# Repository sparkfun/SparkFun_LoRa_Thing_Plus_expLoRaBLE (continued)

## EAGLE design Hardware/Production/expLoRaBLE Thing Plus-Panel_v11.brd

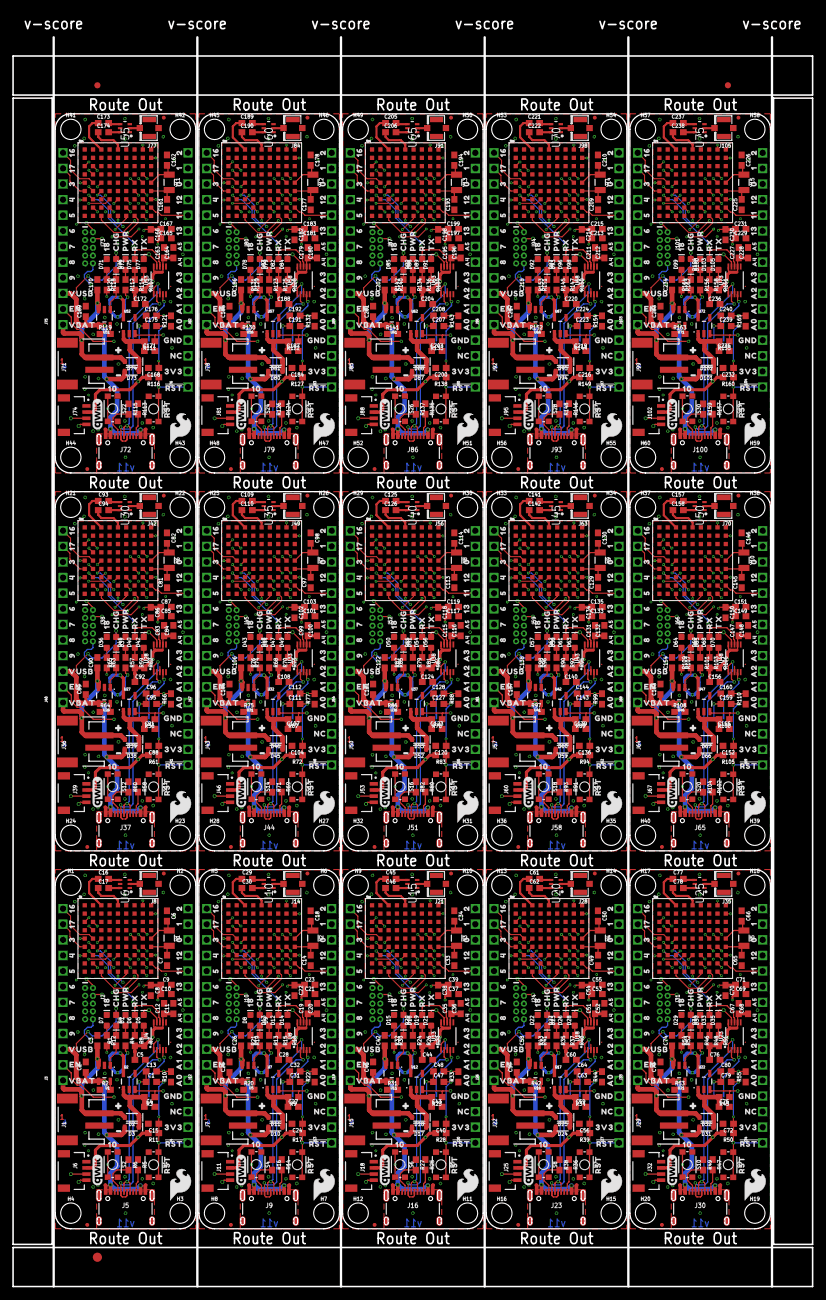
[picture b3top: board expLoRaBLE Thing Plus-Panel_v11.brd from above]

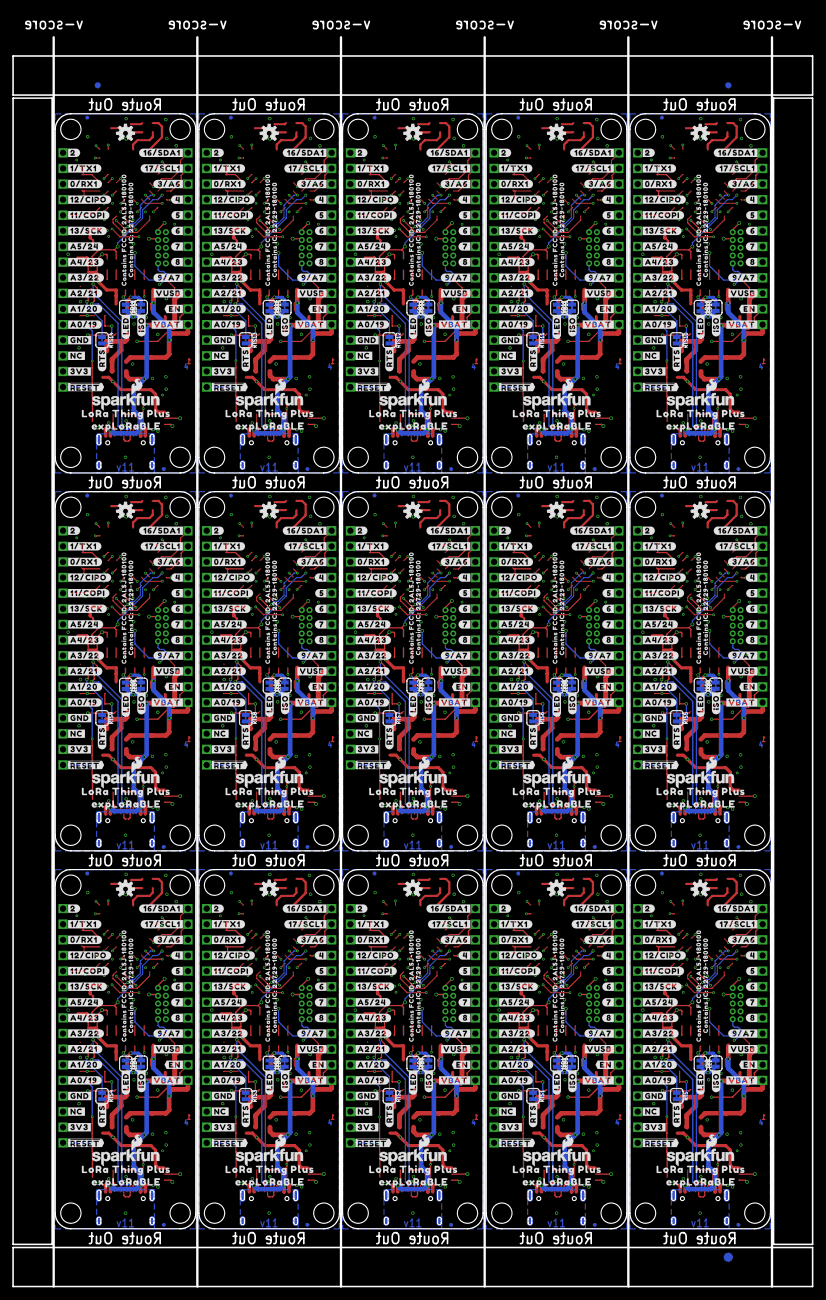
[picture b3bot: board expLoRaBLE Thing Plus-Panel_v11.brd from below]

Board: 4 copper layers, 130.0 x 203.2 mm, 2181 parts (633 on the bottom side), 900 nets.

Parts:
C1, C10, C11, C13, C20, C21, C31, C32, C36, C37, C47, C48, C52, C53, C63, C64, C68, C69, C79, C80, C84, C85, C95, C96, C100, C101, C111, C112, C116, C117, C127, C128, C132, C133, C143, C144, C148, C149, C159, C160, C164, C165, C175, C176, C180, C181, C191, C192, C196, C197, C207, C208, C212, C213, C223, C224, C228, C229, C239, C240: 0.1uF; 0603
C2, C3, C25, C26, C41, C42, C57, C58, C73, C74, C89, C90, C105, C106, C121, C122, C137, C138, C153, C154, C169, C170, C185, C186, C201, C202, C217, C218, C233, C234: 4.7uF; 0603
C4, C5, C9, C23, C27, C28, C39, C43, C44, C55, C59, C60, C71, C75, C76, C87, C91, C92, C103, C107, C108, C119, C123, C124, C135, C139, C140, C151, C155, C156, C167, C171, C172, C183, C187, C188, C199, C203, C204, C215, C219, C220, C231, C235, C236: 1.0uF; 0603
C6, C7, C14, C18, C33, C34, C49, C50, C65, C66, C81, C82, C97, C98, C113, C114, C129, C130, C145, C146, C161, C162, C177, C178, C193, C194, C209, C210, C225, C226: 15pF; 0603
C8, C22, C38, C54, C70, C86, C102, C118, C134, C150, C166, C182, C198, C214, C230: 10uF; 0603
C12, C19, C35, C51, C67, C83, C99, C115, C131, C147, C163, C179, C195, C211, C227: 10nF; 0603
C15, C24, C40, C56, C72, C88, C104, C120, C136, C152, C168, C184, C200, C216, C232: 1nF; 0603
C16, C29, C45, C61, C77, C93, C109, C125, C141, C157, C173, C189, C205, C221, C237: 47pF; 0603
C17, C30, C46, C62, C78, C94, C110, C126, C142, C158, C174, C190, C206, C222, C238: 10pF; 0603
D1, D6, D9, D12, D16, D19, D23, D26, D30, D33, D37, D40, D44, D47, D51, D54, D58, D61, D65, D68, D72, D75, D79, D82, D86, D89, D93, D96, D100, D103: Yellow; LED-0603
D2, D3, D10, D11, D17, D18, D24, D25, D31, D32, D38, D39, D45, D46, D52, D53, D59, D60, D66, D67, D73, D74, D80, D81, D87, D88, D94, D95, D101, D102: 3A/10V/280mV; SOD-323
D4, D13, D20, D27, D34, D41, D48, D55, D62, D69, D76, D83, D90, D97, D104: RED; LED-0603
D5, D14, D21, D28, D35, D42, D49, D56, D63, D70, D77, D84, D91, D98, D105: GREEN; LED-0603
D7, D8, D15, D22, D29, D36, D43, D50, D57, D64, D71, D78, D85, D92, D99: BLUE; LED-0603
E$1, E$2, E$3, E$4: FIDUCIAL-1X2
E$5, E$6: FIDUCIAL-1.5X3
FD1, FD2, FD3, FD4, FD5, FD6, FD7, FD8, FD9, FD10, FD11, FD12, FD13, FD14, FD15, FD16, FD17, FD18, FD19, FD20, FD21, FD22, FD23, FD24, FD25, FD26, FD27, FD28, FD29, FD30, FD31, FD32, FD33, FD34, FD35, FD36, FD37, FD38, FD39, FD40, FD41, FD42, FD43, FD44, FD45, FD46, FD47, FD48, FD49, FD50, FD51, FD52, FD53, FD54, FD55, FD56, FD57, FD58, FD59, FD60: FIDUCIALUFIDUCIAL; FIDUCIAL-MICRO
FRAME1, FRAME3, FRAME5, FRAME7, FRAME9, FRAME11, FRAME13, FRAME15, FRAME17, FRAME19, FRAME21, FRAME23, FRAME25, FRAME27, FRAME29: FRAME-LETTER; CREATIVE_COMMONS
FRAME2, FRAME4, FRAME6, FRAME8, FRAME10, FRAME12, FRAME14, FRAME16, FRAME18, FRAME20, FRAME22, FRAME24, FRAME26, FRAME28, FRAME30: FRAME-LETTERNO_PACKAGE; DUMMY
H1, H2, H3, H4, H5, H6, H7, H8, H9, H10, H11, H12, H13, H14, H15, H16, H17, H18, H19, H20, H21, H22, H23, H24, H25, H26, H27, H28, H29, H30, H31, H32, H33, H34, H35, H36, H37, H38, H39, H40, H41, H42, H43, H44, H45, H46, H47, H48, H49, H50, H51, H52, H53, H54, H55, H56, H57, H58, H59, H60: STAND-OFF
ISO, ISO1, ISO2, ISO3, ISO4, ISO5, ISO6, ISO7, ISO8, ISO9, ISO10, ISO11, ISO12, ISO13, ISO14: JUMPER-SMT_2_NC_TRACE_SILK; SMT-JUMPER_2_NC_TRACE_SILK
J1, J7, J15, J22, J29, J36, J43, J50, J57, J64, J71, J78, J85, J92, J99: JST-2-SMD
J2, J10, J17, J24, J31, J38, J45, J52, J59, J66, J73, J80, J87, J94, J101: CORTEX_DEBUG; 2X5-PTH-1.27MM-NO_SILK
J3, J12, J19, J26, J33, J40, J47, J54, J61, J68, J75, J82, J89, J96, J103: 1X12_SM_SQ_NOSILK
J4, J13, J20, J27, J34, J41, J48, J55, J62, J69, J76, J83, J90, J97, J104: 1X16_SM_SQ_NOSILK
J5, J9, J16, J23, J30, J37, J44, J51, J58, J65, J72, J79, J86, J93, J100: USB Female Type C Connector; USB-C-16P-4LAYER-ISOLATED
J6, J11, J18, J25, J32, J39, J46, J53, J60, J67, J74, J81, J88, J95, J102: QWIIC_RA; JST04_1MM_RA
J8, J14, J21, J28, J35, J42, J49, J56, J63, J70, J77, J84, J91, J98, J105: U.FL
LED, LED1, LED2, LED3, LED4, LED5, LED6, LED7, LED8, LED9, LED10, LED11, LED12, LED13, LED14: JUMPER-SMT_2_NC_TRACE_SILK; SMT-JUMPER_2_NC_TRACE_SILK
LOGO1, LOGO6, LOGO9, LOGO12, LOGO15, LOGO18, LOGO21, LOGO24, LOGO27, LOGO30, LOGO33, LOGO36, LOGO39, LOGO42, LOGO45: OSHW-LOGOS; OSHW-LOGO-S
LOGO2, LOGO4, LOGO7, LOGO10, LOGO13, LOGO16, LOGO19, LOGO22, LOGO25, LOGO28, LOGO31, LOGO34, LOGO37, LOGO40, LOGO43: QWIIC_LOGO_5MM; QWIIC_5MM
LOGO3, LOGO5, LOGO8, LOGO11, LOGO14, LOGO17, LOGO20, LOGO23, LOGO26, LOGO29, LOGO32, LOGO35, LOGO38, LOGO41, LOGO44: SFE_LOGO_NAME_FLAME.1_INCH; SFE_LOGO_NAME_FLAME_.1
R1, R4, R7, R8, R12, R13, R15, R18, R19, R21, R24, R26, R29, R30, R32, R35, R37, R40, R41, R43, R46, R48, R51, R52, R54, R57, R59, R62, R63, R65, R68, R70, R73, R74, R76, R79, R81, R84, R85, R87, R90, R92, R95, R96, R98, R101, R103, R106, R107, R109, R112, R114, R117, R118, R120, R123, R125, R128, R129, R131, R134, R136, R139, R140, R142, R145, R147, R150, R151, R153, R156, R158, R161, R162, R164: 1k; 0603
R2, R20, R31, R42, R53, R64, R75, R86, R97, R108, R119, R130, R141, R152, R163: 2.0k; 0603
R3, R9, R23, R34, R45, R56, R67, R78, R89, R100, R111, R122, R133, R144, R155: 10k; 0603
R5, R6, R14, R16, R25, R27, R36, R38, R47, R49, R58, R60, R69, R71, R80, R82, R91, R93, R102, R104, R113, R115, R124, R126, R135, R137, R146, R148, R157, R159: 5.1k; 0603
R10, R22, R33, R44, R55, R66, R77, R88, R99, R110, R121, R132, R143, R154, R165: 220k; 0603
R11, R17, R28, R39, R50, R61, R72, R83, R94, R105, R116, R127, R138, R149, R160: 100k; 0603
RTS, RTS1, RTS2, RTS3, RTS4, RTS5, RTS6, RTS7, RTS8, RTS9, RTS10, RTS11, RTS12, RTS13, RTS14: JUMPER-SMT_2_NC_TRACE_SILK; SMT-JUMPER_2_NC_TRACE_SILK
S1, S3, S5, S7, S9, S11, S13, S15, S17, S19, S21, S23, S25, S27, S29: RESET; TACTILE_SWITCH_SMD_4.6X2.8MM
S2, S4, S6, S8, S10, S12, S14, S16, S18, S20, S22, S24, S26, S28, S30: USER; TACTILE_SWITCH_SMD_4.6X2.8MM
TP1, TP2, TP3, TP4, TP5, TP6, TP7, TP8, TP9, TP10, TP11, TP12, TP13, TP14, TP15, TP16, TP17, TP18, TP19, TP20, TP21, TP22, TP23, TP24, TP25, TP26, TP27, TP28, TP29, TP30, TP31, TP32, TP33, TP34, TP35, TP36, TP37, TP38, TP39, TP40, TP41, TP42, TP43, TP44, TP45, TP46, TP47, TP48, TP49, TP50, TP51, TP52, TP53, TP54, TP55, TP56, TP57, TP58, TP59, TP60, TP61, TP62, TP63, TP64, TP65, TP66, TP67, TP68, TP69, TP70, TP71, TP72, TP73, TP74, TP75, TP76, TP77, TP78, TP79, TP80, TP81, TP82, TP83, TP84, TP85, TP86, TP87, TP88, TP89, TP90: TEST-POINTTP_15TH_THRU; TP_15TH
U1, U5, U11, U16, U21, U26, U31, U36, U41, U46, U51, U56, U61, U66, U71: MCP73831; SOT23-5
U2, U7, U12, U17, U22, U27, U32, U37, U42, U47, U52, U57, U62, U67, U72: 3.3V; SOT23-5
U3, U9, U14, U19, U24, U29, U34, U39, U44, U49, U54, U59, U64, U69, U74: NM180100; LGA81
U4, U8, U13, U18, U23, U28, U33, U38, U43, U48, U53, U58, U63, U68, U73: CH340E_MSOP10; MSOP10
U6, U10, U15, U20, U25, U30, U35, U40, U45, U50, U55, U60, U65, U70, U75: DPX202700DT-4162A1; RF_4060A1_TDK
U$1, U$115, U$189, U$263, U$337, U$411, U$485, U$559, U$633, U$707, U$781, U$855, U$929, U$1003, U$1077: #16#SDA1#0
U$2, U$113, U$187, U$261, U$335, U$409, U$483, U$557, U$631, U$705, U$779, U$853, U$927, U$1001, U$1075: LORA_THING_PLUS0
U$3, U$114, U$188, U$262, U$336, U$410, U$484, U$558, U$632, U$706, U$780, U$854, U$928, U$1002, U$1076: EXPLORABLE0
U$4, U$116, U$190, U$264, U$338, U$412, U$486, U$560, U$634, U$708, U$782, U$856, U$930, U$1004, U$1078: #17#SCL1#0
U$5, U$117, U$191, U$265, U$339, U$413, U$487, U$561, U$635, U$709, U$783, U$857, U$931, U$1005, U$1079: #3#A6#0
U$6, U$118, U$192, U$266, U$340, U$414, U$488, U$562, U$636, U$710, U$784, U$858, U$932, U$1006, U$1080: #4#0
U$7, U$119, U$193, U$267, U$341, U$415, U$489, U$563, U$637, U$711, U$785, U$859, U$933, U$1007, U$1081: #5#0
U$8, U$120, U$194, U$268, U$342, U$416, U$490, U$564, U$638, U$712, U$786, U$860, U$934, U$1008, U$1082: #6#0
U$9, U$121, U$195, U$269, U$343, U$417, U$491, U$565, U$639, U$713, U$787, U$861, U$935, U$1009, U$1083: #7#0
U$10, U$122, U$196, U$270, U$344, U$418, U$492, U$566, U$640, U$714, U$788, U$862, U$936, U$1010, U$1084: #8#0
U$11, U$123, U$197, U$271, U$345, U$419, U$493, U$567, U$641, U$715, U$789, U$863, U$937, U$1011, U$1085: #9#A7#0
U$12, U$124, U$198, U$272, U$346, U$420, U$494, U$568, U$642, U$716, U$790, U$864, U$938, U$1012, U$1086: #VUSB#0
U$13, U$125, U$199, U$273, U$347, U$421, U$495, U$569, U$643, U$717, U$791, U$865, U$939, U$1013, U$1087: VUSB0
U$14, U$126, U$200, U$274, U$348, U$422, U$496, U$570, U$644, U$718, U$792, U$866, U$940, U$1014, U$1088: #EN#0
U$15, U$127, U$201, U$275, U$349, U$423, U$497, U$571, U$645, U$719, U$793, U$867, U$941, U$1015, U$1089: #VBAT#0
U$16, U$128, U$202, U$276, U$350, U$424, U$498, U$572, U$646, U$720, U$794, U$868, U$942, U$1016, U$1090: #2#0
U$17, U$129, U$203, U$277, U$351, U$425, U$499, U$573, U$647, U$721, U$795, U$869, U$943, U$1017, U$1091: #1#TX1#0
U$18, U$130, U$204, U$278, U$352, U$426, U$500, U$574, U$648, U$722, U$796, U$870, U$944, U$1018, U$1092: #0#RX1#0
U$19, U$131, U$205, U$279, U$353, U$427, U$501, U$575, U$649, U$723, U$797, U$871, U$945, U$1019, U$1093: #12#CIPO#0
U$20, U$132, U$206, U$280, U$354, U$428, U$502, U$576, U$650, U$724, U$798, U$872, U$946, U$1020, U$1094: #11#COPI#0
U$21, U$133, U$207, U$281, U$355, U$429, U$503, U$577, U$651, U$725, U$799, U$873, U$947, U$1021, U$1095: #13#SCK#0
U$22, U$146, U$220, U$294, U$368, U$442, U$516, U$590, U$664, U$738, U$812, U$886, U$960, U$1034, U$1108: CONTAINS_FCC_ID#_2AL5J#1801000
U$23, U$147, U$221, U$295, U$369, U$443, U$517, U$591, U$665, U$739, U$813, U$887, U$961, U$1035, U$1109: CONTAINS_IC#_22729#1801000
U$24, U$148, U$222, U$296, U$370, U$444, U$518, U$592, U$666, U$740, U$814, U$888, U$962, U$1036, U$1110: #RTS#0
U$25, U$65, U$149, U$223, U$297, U$371, U$445, U$519, U$593, U$667, U$741, U$815, U$889, U$963, U$1037: SFE_LOGO_FLAME_.2
U$26, U$64, U$150, U$224, U$298, U$372, U$446, U$520, U$594, U$668, U$742, U$816, U$890, U$964, U$1038: FOUR_LAYER_WARNING
U$27, U$66, U$151, U$225, U$299, U$373, U$447, U$521, U$595, U$669, U$743, U$817, U$891, U$965, U$1039: 160
U$28, U$134, U$208, U$282, U$356, U$430, U$504, U$578, U$652, U$726, U$800, U$874, U$948, U$1022, U$1096: #GND#0
U$29, U$135, U$209, U$283, U$357, U$431, U$505, U$579, U$653, U$727, U$801, U$875, U$949, U$1023, U$1097: #NC#0
U$30, U$136, U$210, U$284, U$358, U$432, U$506, U$580, U$654, U$728, U$802, U$876, U$950, U$1024, U$1098: #3V3#0
U$31, U$137, U$211, U$285, U$359, U$433, U$507, U$581, U$655, U$729, U$803, U$877, U$951, U$1025, U$1099: ##RESET##0
U$32, U$138, U$212, U$286, U$360, U$434, U$508, U$582, U$656, U$730, U$804, U$878, U$952, U$1026, U$1100: #LED#0
U$33, U$140, U$214, U$288, U$362, U$436, U$510, U$584, U$658, U$732, U$806, U$880, U$954, U$1028, U$1102: #A0#19#0
U$34, U$139, U$213, U$287, U$361, U$435, U$509, U$583, U$657, U$731, U$805, U$879, U$953, U$1027, U$1101: #ISO#0
U$35, U$141, U$215, U$289, U$363, U$437, U$511, U$585, U$659, U$733, U$807, U$881, U$955, U$1029, U$1103: #A1#20#0
U$36, U$142, U$216, U$290, U$364, U$438, U$512, U$586, U$660, U$734, U$808, U$882, U$956, U$1030, U$1104: #A2#21#0
U$37, U$143, U$217, U$291, U$365, U$439, U$513, U$587, U$661, U$735, U$809, U$883, U$957, U$1031, U$1105: #A3#22#0
U$38, U$144, U$218, U$292, U$366, U$440, U$514, U$588, U$662, U$736, U$810, U$884, U$958, U$1032, U$1106: #A4#23#0
U$39, U$145, U$219, U$293, U$367, U$441, U$515, U$589, U$663, U$737, U$811, U$885, U$959, U$1033, U$1107: #A5#24#0
U$40, U$69, U$152, U$226, U$300, U$374, U$448, U$522, U$596, U$670, U$744, U$818, U$892, U$966, U$1040: 170
U$41, U$70, U$153, U$227, U$301, U$375, U$449, U$523, U$597, U$671, U$745, U$819, U$893, U$967, U$1041: 30
U$42, U$71, U$154, U$228, U$302, U$376, U$450, U$524, U$598, U$672, U$746, U$820, U$894, U$968, U$1042: 40
U$43, U$72, U$155, U$229, U$303, U$377, U$451, U$525, U$599, U$673, U$747, U$821, U$895, U$969, U$1043: 50
U$44, U$73, U$156, U$230, U$304, U$378, U$452, U$526, U$600, U$674, U$748, U$822, U$896, U$970, U$1044: 60
U$45, U$74, U$157, U$231, U$305, U$379, U$453, U$527, U$601, U$675, U$749, U$823, U$897, U$971, U$1045: 70
U$46, U$75, U$158, U$232, U$306, U$380, U$454, U$528, U$602, U$676, U$750, U$824, U$898, U$972, U$1046: 80
U$47, U$76, U$159, U$233, U$307, U$381, U$455, U$529, U$603, U$677, U$751, U$825, U$899, U$973, U$1047: 90
U$48, U$78, U$160, U$234, U$308, U$382, U$456, U$530, U$604, U$678, U$752, U$826, U$900, U$974, U$1048: EN0
U$49, U$79, U$161, U$235, U$309, U$383, U$457, U$531, U$605, U$679, U$753, U$827, U$901, U$975, U$1049: VBAT0
U$50, U$80, U$162, U$236, U$310, U$384, U$458, U$532, U$606, U$680, U$754, U$828, U$902, U$976, U$1050: 20
U$51, U$81, U$163, U$237, U$311, U$385, U$459, U$533, U$607, U$681, U$755, U$829, U$903, U$977, U$1051: 10
U$52, U$82, U$164, U$238, U$312, U$386, U$460, U$534, U$608, U$682, U$756, U$830, U$904, U$978, U$1052: 00
U$53, U$83, U$165, U$239, U$313, U$387, U$461, U$535, U$609, U$683, U$757, U$831, U$905, U$979, U$1053: 120
U$54, U$84, U$166, U$240, U$314, U$388, U$462, U$536, U$610, U$684, U$758, U$832, U$906, U$980, U$1054: 110
U$55, U$85, U$167, U$241, U$315, U$389, U$463, U$537, U$611, U$685, U$759, U$833, U$907, U$981, U$1055: 130
U$56, U$86, U$168, U$242, U$316, U$390, U$464, U$538, U$612, U$686, U$760, U$834, U$908, U$982, U$1056: A50
U$57, U$87, U$169, U$243, U$317, U$391, U$465, U$539, U$613, U$687, U$761, U$835, U$909, U$983, U$1057: A40
U$58, U$88, U$170, U$244, U$318, U$392, U$466, U$540, U$614, U$688, U$762, U$836, U$910, U$984, U$1058: A30
U$59, U$89, U$171, U$245, U$319, U$393, U$467, U$541, U$615, U$689, U$763, U$837, U$911, U$985, U$1059: A20
U$60, U$90, U$172, U$246, U$320, U$394, U$468, U$542, U$616, U$690, U$764, U$838, U$912, U$986, U$1060: A10
U$61, U$91, U$173, U$247, U$321, U$395, U$469, U$543, U$617, U$691, U$765, U$839, U$913, U$987, U$1061: A00
U$62, U$108, U$182, U$256, U$330, U$404, U$478, U$552, U$626, U$700, U$774, U$848, U$922, U$996, U$1070: 180
U$63, U$92, U$174, U$248, U$322, U$396, U$470, U$544, U$618, U$692, U$766, U$840, U$914, U$988, U$1062: GND0
U$67, U$109, U$183, U$257, U$331, U$405, U$479, U$553, U$627, U$701, U$775, U$849, U$923, U$997, U$1071: CHG0
U$68, U$110, U$184, U$258, U$332, U$406, U$480, U$554, U$628, U$702, U$776, U$850, U$924, U$998, U$1072: PWR0
U$77, U$93, U$175, U$249, U$323, U$397, U$471, U$545, U$619, U$693, U$767, U$841, U$915, U$989, U$1063: NC0
U$94, U$102, U$176, U$250, U$324, U$398, U$472, U$546, U$620, U$694, U$768, U$842, U$916, U$990, U$1064: 3V30
U$95, U$103, U$177, U$251, U$325, U$399, U$473, U$547, U$621, U$695, U$769, U$843, U$917, U$991, U$1065: #RST#0
U$96, U$104, U$178, U$252, U$326, U$400, U$474, U$548, U$622, U$696, U$770, U$844, U$918, U$992, U$1066: RST0
U$97, U$105, U$179, U$253, U$327, U$401, U$475, U$549, U$623, U$697, U$771, U$845, U$919, U$993, U$1067: 100
U$98, U$106, U$180, U$254, U$328, U$402, U$476, U$550, U$624, U$698, U$772, U$846, U$920, U$994, U$1068: #0
U$99, U$107, U$181, U$255, U$329, U$403, U$477, U$551, U$625, U$699, U$773, U$847, U$921, U$995, U$1069: #_0
U$100, U$111, U$185, U$259, U$333, U$407, U$481, U$555, U$629, U$703, U$777, U$851, U$925, U$999, U$1073: RX0
U$101, U$112, U$186, U$260, U$334, U$408, U$482, U$556, U$630, U$704, U$778, U$852, U$926, U$1000, U$1074: TX0
Y1, Y2, Y3, Y4, Y5, Y6, Y7, Y8, Y9, Y10, Y11, Y12, Y13, Y14, Y15: 32.768kHz; CRYSTAL-SMD-3.2X1.5MM

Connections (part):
3.3V: C5.1, C8.1, C9.1, C10.1, C11.1, C12.1, ISO.1, J2.1, J4.2, J6.2, LED.2, R7.2, R8.2, R11.2, U3.H2, U3.H4, U3.H6, U3.H8, U4.7, U4.10
3.3V1: C19.1, C20.1, C21.1, C22.1, C23.1, C28.1, ISO1.1, J10.1, J11.2, J13.2, LED1.2, R15.2, R17.2, R18.2, U8.7, U8.10, U9.H2, U9.H4, U9.H6, U9.H8
3.3V2: C35.1, C36.1, C37.1, C38.1, C39.1, C44.1, ISO2.1, J17.1, J18.2, J20.2, LED2.2, R26.2, R28.2, R29.2, U13.7, U13.10, U14.H2, U14.H4, U14.H6, U14.H8
3.3V3: C51.1, C52.1, C53.1, C54.1, C55.1, C60.1, ISO3.1, J24.1, J25.2, J27.2, LED3.2, R37.2, R39.2, R40.2, U18.7, U18.10, U19.H2, U19.H4, U19.H6, U19.H8
3.3V4: C67.1, C68.1, C69.1, C70.1, C71.1, C76.1, ISO4.1, J31.1, J32.2, J34.2, LED4.2, R48.2, R50.2, R51.2, U23.7, U23.10, U24.H2, U24.H4, U24.H6, U24.H8
3.3V5: C83.1, C84.1, C85.1, C86.1, C87.1, C92.1, ISO5.1, J38.1, J39.2, J41.2, LED5.2, R59.2, R61.2, R62.2, U28.7, U28.10, U29.H2, U29.H4, U29.H6, U29.H8
3.3V6: C99.1, C100.1, C101.1, C102.1, C103.1, C108.1, ISO6.1, J45.1, J46.2, J48.2, LED6.2, R70.2, R72.2, R73.2, U33.7, U33.10, U34.H2, U34.H4, U34.H6, U34.H8
3.3V7: C115.1, C116.1, C117.1, C118.1, C119.1, C124.1, ISO7.1, J52.1, J53.2, J55.2, LED7.2, R81.2, R83.2, R84.2, U38.7, U38.10, U39.H2, U39.H4, U39.H6, U39.H8
3.3V8: C131.1, C132.1, C133.1, C134.1, C135.1, C140.1, ISO8.1, J59.1, J60.2, J62.2, LED8.2, R92.2, R94.2, R95.2, U43.7, U43.10, U44.H2, U44.H4, U44.H6, U44.H8
3.3V9: C147.1, C148.1, C149.1, C150.1, C151.1, C156.1, ISO9.1, J66.1, J67.2, J69.2, LED9.2, R103.2, R105.2, R106.2, U48.7, U48.10, U49.H2, U49.H4, U49.H6, U49.H8
3.3V10: C163.1, C164.1, C165.1, C166.1, C167.1, C172.1, ISO10.1, J73.1, J74.2, J76.2, LED10.2, R114.2, R116.2, R117.2, U53.7, U53.10, U54.H2, U54.H4, U54.H6, U54.H8
3.3V11: C179.1, C180.1, C181.1, C182.1, C183.1, C188.1, ISO11.1, J80.1, J81.2, J83.2, LED11.2, R125.2, R127.2, R128.2, U58.7, U58.10, U59.H2, U59.H4, U59.H6, U59.H8
3.3V12: C195.1, C196.1, C197.1, C198.1, C199.1, C204.1, ISO12.1, J87.1, J88.2, J90.2, LED12.2, R136.2, R138.2, R139.2, U63.7, U63.10, U64.H2, U64.H4, U64.H6, U64.H8
3.3V13: C211.1, C212.1, C213.1, C214.1, C215.1, C220.1, ISO13.1, J94.1, J95.2, J97.2, LED13.2, R147.2, R149.2, R150.2, U68.7, U68.10, U69.H2, U69.H4, U69.H6, U69.H8
3.3V14: C227.1, C228.1, C229.1, C230.1, C231.1, C236.1, ISO14.1, J101.1, J102.2, J104.2, LED14.2, R158.2, R160.2, R161.2, U73.7, U73.10, U74.H2, U74.H4, U74.H6, U74.H8
!RESET: C1.2, C15.1, J2.10, J4.1, R11.1, S1.3, S1.4, U3.C1
!RESET1: C24.1, C31.2, J10.10, J13.1, R17.1, S3.3, S3.4, U9.C1
!RESET2: C40.1, C47.2, J17.10, J20.1, R28.1, S5.3, S5.4, U14.C1
!RESET3: C56.1, C63.2, J24.10, J27.1, R39.1, S7.3, S7.4, U19.C1
!RESET4: C72.1, C79.2, J31.10, J34.1, R50.1, S9.3, S9.4, U24.C1
!RESET5: C88.1, C95.2, J38.10, J41.1, R61.1, S11.3, S11.4, U29.C1
!RESET6: C104.1, C111.2, J45.10, J48.1, R72.1, S13.3, S13.4, U34.C1
!RESET7: C120.1, C127.2, J52.10, J55.1, R83.1, S15.3, S15.4, U39.C1
!RESET8: C136.1, C143.2, J59.10, J62.1, R94.1, S17.3, S17.4, U44.C1
!RESET9: C152.1, C159.2, J66.10, J69.1, R105.1, S19.3, S19.4, U49.C1
!RESET10: C168.1, C175.2, J73.10, J76.1, R116.1, S21.3, S21.4, U54.C1
!RESET11: C184.1, C191.2, J80.10, J83.1, R127.1, S23.3, S23.4, U59.C1
!RESET12: C200.1, C207.2, J87.10, J90.1, R138.1, S25.3, S25.4, U64.C1
!RESET13: C216.1, C223.2, J94.10, J97.1, R149.1, S27.3, S27.4, U69.C1
!RESET14: C232.1, C239.2, J101.10, J104.1, R160.1, S29.3, S29.4, U74.C1
!RTS: RTS.1, U4.4
!RTS1: RTS1.1, U8.4
!RTS2: RTS2.1, U13.4
!RTS3: RTS3.1, U18.4
!RTS4: RTS4.1, U23.4
!RTS5: RTS5.1, U28.4
!RTS6: RTS6.1, U33.4
!RTS7: RTS7.1, U38.4
!RTS8: RTS8.1, U43.4
!RTS9: RTS9.1, U48.4
!RTS10: RTS10.1, U53.4
!RTS11: RTS11.1, U58.4
!RTS12: RTS12.1, U63.4
!RTS13: RTS13.1, U68.4
!RTS14: RTS14.1, U73.4
BOOT: C13.2, R10.2, U3.J7
BOOT1: C32.2, R22.2, U9.J7
BOOT2: C48.2, R33.2, U14.J7
BOOT3: C64.2, R44.2, U19.J7
BOOT4: C80.2, R55.2, U24.J7
BOOT5: C96.2, R66.2, U29.J7
BOOT6: C112.2, R77.2, U34.J7
BOOT7: C128.2, R88.2, U39.J7
BOOT8: C144.2, R99.2, U44.J7
BOOT9: C160.2, R110.2, U49.J7
BOOT10: C176.2, R121.2, U54.J7
BOOT11: C192.2, R132.2, U59.J7
BOOT12: C208.2, R143.2, U64.J7
BOOT13: C224.2, R154.2, U69.J7
BOOT14: C240.2, R165.2, U74.J7
BT_RF: C17.1, U3.A5
BT_RF1: C30.1, U9.A5
BT_RF2: C46.1, U14.A5
BT_RF3: C62.1, U19.A5
BT_RF4: C78.1, U24.A5
BT_RF5: C94.1, U29.A5
BT_RF6: C110.1, U34.A5
BT_RF7: C126.1, U39.A5
BT_RF8: C142.1, U44.A5
BT_RF9: C158.1, U49.A5
BT_RF10: C174.1, U54.A5
BT_RF11: C190.1, U59.A5
BT_RF12: C206.1, U64.A5
BT_RF13: C222.1, U69.A5
BT_RF14: C238.1, U74.A5
CC1: J5.A5, R6.2
CC2: J5.B5, R5.2
CC3: J9.B5, R14.2
CC4: J9.A5, R16.2
CC5: J16.B5, R25.2
CC6: J16.A5, R27.2
CC7: J23.B5, R36.2
CC8: J23.A5, R38.2
CC9: J30.B5, R47.2
CC10: J30.A5, R49.2
CC11: J37.B5, R58.2
CC12: J37.A5, R60.2
CC13: J44.B5, R69.2
CC14: J44.A5, R71.2
CC15: J51.B5, R80.2
CC16: J51.A5, R82.2
CC17: J58.B5, R91.2
CC18: J58.A5, R93.2
CC19: J65.B5, R102.2
CC20: J65.A5, R104.2
CC21: J72.B5, R113.2
CC22: J72.A5, R115.2
CC23: J79.B5, R124.2
CC24: J79.A5, R126.2
CC25: J86.B5, R135.2
CC26: J86.A5, R137.2
CC27: J93.B5, R146.2
CC28: J93.A5, R148.2
CC29: J100.B5, R157.2
CC30: J100.A5, R159.2
D10/SWCH: S2.1, S2.2, U3.J6
D10/SWCH1: S4.1, S4.2, U9.J6
D10/SWCH2: S6.1, S6.2, U14.J6
D10/SWCH3: S8.1, S8.2, U19.J6
D10/SWCH4: S10.1, S10.2, U24.J6
D10/SWCH5: S12.1, S12.2, U29.J6
D10/SWCH6: S14.1, S14.2, U34.J6
D10/SWCH7: S16.1, S16.2, U39.J6
D10/SWCH8: S18.1, S18.2, U44.J6
D10/SWCH9: S20.1, S20.2, U49.J6
D10/SWCH10: S22.1, S22.2, U54.J6
D10/SWCH11: S24.1, S24.2, U59.J6
D10/SWCH12: S26.1, S26.2, U64.J6
D10/SWCH13: S28.1, S28.2, U69.J6
D10/SWCH14: S30.1, S30.2, U74.J6
D14/QWIIC_SDA: J6.3, TP5.P$1, U3.G1
D14/QWIIC_SDA1: J11.3, TP10.P$1, U9.G1
D14/QWIIC_SDA2: J18.3, TP16.P$1, U14.G1
D14/QWIIC_SDA3: J25.3, TP22.P$1, U19.G1
D14/QWIIC_SDA4: J32.3, TP28.P$1, U24.G1
D14/QWIIC_SDA5: J39.3, TP34.P$1, U29.G1
D14/QWIIC_SDA6: J46.3, TP40.P$1, U34.G1
D14/QWIIC_SDA7: J53.3, TP46.P$1, U39.G1
D14/QWIIC_SDA8: J60.3, TP52.P$1, U44.G1
D14/QWIIC_SDA9: J67.3, TP58.P$1, U49.G1
D14/QWIIC_SDA10: J74.3, TP64.P$1, U54.G1
D14/QWIIC_SDA11: J81.3, TP70.P$1, U59.G1
D14/QWIIC_SDA12: J88.3, TP76.P$1, U64.G1
D14/QWIIC_SDA13: J95.3, TP82.P$1, U69.G1
D14/QWIIC_SDA14: J102.3, TP88.P$1, U74.G1
D+1: J5.A6, J5.B6, U4.1
D+2: J9.A6, J9.B6, U8.1
D+3: J16.A6, J16.B6, U13.1
D+4: J23.A6, J23.B6, U18.1
D+5: J30.A6, J30.B6, U23.1
D+6: J37.A6, J37.B6, U28.1
D+7: J44.A6, J44.B6, U33.1
D+8: J51.A6, J51.B6, U38.1
D+9: J58.A6, J58.B6, U43.1
D+10: J65.A6, J65.B6, U48.1
D+11: J72.A6, J72.B6, U53.1
D+12: J79.A6, J79.B6, U58.1
D+13: J86.A6, J86.B6, U63.1
D+14: J93.A6, J93.B6, U68.1
D+15: J100.A6, J100.B6, U73.1
D-1: J5.A7, J5.B7, U4.2
D-2: J9.A7, J9.B7, U8.2
D-3: J16.A7, J16.B7, U13.2
D-4: J23.A7, J23.B7, U18.2
D-5: J30.A7, J30.B7, U23.2
D-6: J37.A7, J37.B7, U28.2
D-7: J44.A7, J44.B7, U33.2
D-8: J51.A7, J51.B7, U38.2
D-9: J58.A7, J58.B7, U43.2
D-10: J65.A7, J65.B7, U48.2
D-11: J72.A7, J72.B7, U53.2
D-12: J79.A7, J79.B7, U58.2
D-13: J86.A7, J86.B7, U63.2
D-14: J93.A7, J93.B7, U68.2
D-15: J100.A7, J100.B7, U73.2
EN: J3.2, R3.1, U2.3
EN1: J12.2, R9.1, U7.3
EN2: J19.2, R23.1, U12.3
EN3: J26.2, R34.1, U17.3
EN4: J33.2, R45.1, U22.3
EN5: J40.2, R56.1, U27.3
EN6: J47.2, R67.1, U32.3
EN7: J54.2, R78.1, U37.3
EN8: J61.2, R89.1, U42.3
EN9: J68.2, R100.1, U47.3
EN10: J75.2, R111.1, U52.3
EN11: J82.2, R122.1, U57.3
EN12: J89.2, R133.1, U62.3
EN13: J96.2, R144.1, U67.3
EN14: J103.2, R155.1, U72.3
GND: C2.2, C3.2, C4.2, C5.2, C6.1, C7.1, C8.2, C9.2, C10.2, C11.2, C12.2, C15.2, D4.C, D7.C, J1.1, J2.3, J2.5, J2.9, J4.4, J5.GND, J5.GND2, J6.1, J8.1, J8.2, R2.1, R5.1, R6.1, R10.1, S1.1, S1.2, S2.3, S2.4, U1.2, U2.2, U3.A2, U3.A4, U3.A6, U3.B1, U3.B2, U3.B3, U3.B4, U3.B5, U3.B6, U3.B7, U3.D1, U3.D4, U3.D5, U3.D6, U3.D9, U3.E4, U3.E5, U3.E6, U3.F4, U3.F5, U3.F6, U3.H3, U3.H5, U3.H7, U3.J1, U3.J9, U4.3, U6.1, U6.3, U6.5
GND1: C14.1, C18.1, C19.2, C20.2, C21.2, C22.2, C23.2, C24.2, C25.2, C26.2, C27.2, C28.2, D8.C, D13.C, J7.1, J9.GND, J9.GND2, J10.3, J10.5, J10.9, J11.1, J13.4, J14.1, J14.2, R14.1, R16.1, R20.1, R22.1, S3.1, S3.2, S4.3, S4.4, U5.2, U7.2, U8.3, U9.A2, U9.A4, U9.A6, U9.B1, U9.B2, U9.B3, U9.B4, U9.B5, U9.B6, U9.B7, U9.D1, U9.D4, U9.D5, U9.D6, U9.D9, U9.E4, U9.E5, U9.E6, U9.F4, U9.F5, U9.F6, U9.H3, U9.H5, U9.H7, U9.J1, U9.J9, U10.1, U10.3, U10.5
GND2: C33.1, C34.1, C35.2, C36.2, C37.2, C38.2, C39.2, C40.2, C41.2, C42.2, C43.2, C44.2, D15.C, D20.C, J15.1, J16.GND, J16.GND2, J17.3, J17.5, J17.9, J18.1, J20.4, J21.1, J21.2, R25.1, R27.1, R31.1, R33.1, S5.1, S5.2, S6.3, S6.4, U11.2, U12.2, U13.3, U14.A2, U14.A4, U14.A6, U14.B1, U14.B2, U14.B3, U14.B4, U14.B5, U14.B6, U14.B7, U14.D1, U14.D4, U14.D5, U14.D6, U14.D9, U14.E4, U14.E5, U14.E6, U14.F4, U14.F5, U14.F6, U14.H3, U14.H5, U14.H7, U14.J1, U14.J9, U15.1, U15.3, U15.5
GND3: C49.1, C50.1, C51.2, C52.2, C53.2, C54.2, C55.2, C56.2, C57.2, C58.2, C59.2, C60.2, D22.C, D27.C, J22.1, J23.GND, J23.GND2, J24.3, J24.5, J24.9, J25.1, J27.4, J28.1, J28.2, R36.1, R38.1, R42.1, R44.1, S7.1, S7.2, S8.3, S8.4, U16.2, U17.2, U18.3, U19.A2, U19.A4, U19.A6, U19.B1, U19.B2, U19.B3, U19.B4, U19.B5, U19.B6, U19.B7, U19.D1, U19.D4, U19.D5, U19.D6, U19.D9, U19.E4, U19.E5, U19.E6, U19.F4, U19.F5, U19.F6, U19.H3, U19.H5, U19.H7, U19.J1, U19.J9, U20.1, U20.3, U20.5
GND4: C65.1, C66.1, C67.2, C68.2, C69.2, C70.2, C71.2, C72.2, C73.2, C74.2, C75.2, C76.2, D29.C, D34.C, J29.1, J30.GND, J30.GND2, J31.3, J31.5, J31.9, J32.1, J34.4, J35.1, J35.2, R47.1, R49.1, R53.1, R55.1, S9.1, S9.2, S10.3, S10.4, U21.2, U22.2, U23.3, U24.A2, U24.A4, U24.A6, U24.B1, U24.B2, U24.B3, U24.B4, U24.B5, U24.B6, U24.B7, U24.D1, U24.D4, U24.D5, U24.D6, U24.D9, U24.E4, U24.E5, U24.E6, U24.F4, U24.F5, U24.F6, U24.H3, U24.H5, U24.H7, U24.J1, U24.J9, U25.1, U25.3, U25.5
GND5: C81.1, C82.1, C83.2, C84.2, C85.2, C86.2, C87.2, C88.2, C89.2, C90.2, C91.2, C92.2, D36.C, D41.C, J36.1, J37.GND, J37.GND2, J38.3, J38.5, J38.9, J39.1, J41.4, J42.1, J42.2, R58.1, R60.1, R64.1, R66.1, S11.1, S11.2, S12.3, S12.4, U26.2, U27.2, U28.3, U29.A2, U29.A4, U29.A6, U29.B1, U29.B2, U29.B3, U29.B4, U29.B5, U29.B6, U29.B7, U29.D1, U29.D4, U29.D5, U29.D6, U29.D9, U29.E4, U29.E5, U29.E6, U29.F4, U29.F5, U29.F6, U29.H3, U29.H5, U29.H7, U29.J1, U29.J9, U30.1, U30.3, U30.5
GND6: C97.1, C98.1, C99.2, C100.2, C101.2, C102.2, C103.2, C104.2, C105.2, C106.2, C107.2, C108.2, D43.C, D48.C, J43.1, J44.GND, J44.GND2, J45.3, J45.5, J45.9, J46.1, J48.4, J49.1, J49.2, R69.1, R71.1, R75.1, R77.1, S13.1, S13.2, S14.3, S14.4, U31.2, U32.2, U33.3, U34.A2, U34.A4, U34.A6, U34.B1, U34.B2, U34.B3, U34.B4, U34.B5, U34.B6, U34.B7, U34.D1, U34.D4, U34.D5, U34.D6, U34.D9, U34.E4, U34.E5, U34.E6, U34.F4, U34.F5, U34.F6, U34.H3, U34.H5, U34.H7, U34.J1, U34.J9, U35.1, U35.3, U35.5
GND7: C113.1, C114.1, C115.2, C116.2, C117.2, C118.2, C119.2, C120.2, C121.2, C122.2, C123.2, C124.2, D50.C, D55.C, J50.1, J51.GND, J51.GND2, J52.3, J52.5, J52.9, J53.1, J55.4, J56.1, J56.2, R80.1, R82.1, R86.1, R88.1, S15.1, S15.2, S16.3, S16.4, U36.2, U37.2, U38.3, U39.A2, U39.A4, U39.A6, U39.B1, U39.B2, U39.B3, U39.B4, U39.B5, U39.B6, U39.B7, U39.D1, U39.D4, U39.D5, U39.D6, U39.D9, U39.E4, U39.E5, U39.E6, U39.F4, U39.F5, U39.F6, U39.H3, U39.H5, U39.H7, U39.J1, U39.J9, U40.1, U40.3, U40.5
GND8: C129.1, C130.1, C131.2, C132.2, C133.2, C134.2, C135.2, C136.2, C137.2, C138.2, C139.2, C140.2, D57.C, D62.C, J57.1, J58.GND, J58.GND2, J59.3, J59.5, J59.9, J60.1, J62.4, J63.1, J63.2, R91.1, R93.1, R97.1, R99.1, S17.1, S17.2, S18.3, S18.4, U41.2, U42.2, U43.3, U44.A2, U44.A4, U44.A6, U44.B1, U44.B2, U44.B3, U44.B4, U44.B5, U44.B6, U44.B7, U44.D1, U44.D4, U44.D5, U44.D6, U44.D9, U44.E4, U44.E5, U44.E6, U44.F4, U44.F5, U44.F6, U44.H3, U44.H5, U44.H7, U44.J1, U44.J9, U45.1, U45.3, U45.5
GND9: C145.1, C146.1, C147.2, C148.2, C149.2, C150.2, C151.2, C152.2, C153.2, C154.2, C155.2, C156.2, D64.C, D69.C, J64.1, J65.GND, J65.GND2, J66.3, J66.5, J66.9, J67.1, J69.4, J70.1, J70.2, R102.1, R104.1, R108.1, R110.1, S19.1, S19.2, S20.3, S20.4, U46.2, U47.2, U48.3, U49.A2, U49.A4, U49.A6, U49.B1, U49.B2, U49.B3, U49.B4, U49.B5, U49.B6, U49.B7, U49.D1, U49.D4, U49.D5, U49.D6, U49.D9, U49.E4, U49.E5, U49.E6, U49.F4, U49.F5, U49.F6, U49.H3, U49.H5, U49.H7, U49.J1, U49.J9, U50.1, U50.3, U50.5
GND10: C161.1, C162.1, C163.2, C164.2, C165.2, C166.2, C167.2, C168.2, C169.2, C170.2, C171.2, C172.2, D71.C, D76.C, J71.1, J72.GND, J72.GND2, J73.3, J73.5, J73.9, J74.1, J76.4, J77.1, J77.2, R113.1, R115.1, R119.1, R121.1, S21.1, S21.2, S22.3, S22.4, U51.2, U52.2, U53.3, U54.A2, U54.A4, U54.A6, U54.B1, U54.B2, U54.B3, U54.B4, U54.B5, U54.B6, U54.B7, U54.D1, U54.D4, U54.D5, U54.D6, U54.D9, U54.E4, U54.E5, U54.E6, U54.F4, U54.F5, U54.F6, U54.H3, U54.H5, U54.H7, U54.J1, U54.J9, U55.1, U55.3, U55.5
GND11: C177.1, C178.1, C179.2, C180.2, C181.2, C182.2, C183.2, C184.2, C185.2, C186.2, C187.2, C188.2, D78.C, D83.C, J78.1, J79.GND, J79.GND2, J80.3, J80.5, J80.9, J81.1, J83.4, J84.1, J84.2, R124.1, R126.1, R130.1, R132.1, S23.1, S23.2, S24.3, S24.4, U56.2, U57.2, U58.3, U59.A2, U59.A4, U59.A6, U59.B1, U59.B2, U59.B3, U59.B4, U59.B5, U59.B6, U59.B7, U59.D1, U59.D4, U59.D5, U59.D6, U59.D9, U59.E4, U59.E5, U59.E6, U59.F4, U59.F5, U59.F6, U59.H3, U59.H5, U59.H7, U59.J1, U59.J9, U60.1, U60.3, U60.5
GND12: C193.1, C194.1, C195.2, C196.2, C197.2, C198.2, C199.2, C200.2, C201.2, C202.2, C203.2, C204.2, D85.C, D90.C, J85.1, J86.GND, J86.GND2, J87.3, J87.5, J87.9, J88.1, J90.4, J91.1, J91.2, R135.1, R137.1, R141.1, R143.1, S25.1, S25.2, S26.3, S26.4, U61.2, U62.2, U63.3, U64.A2, U64.A4, U64.A6, U64.B1, U64.B2, U64.B3, U64.B4, U64.B5, U64.B6, U64.B7, U64.D1, U64.D4, U64.D5, U64.D6, U64.D9, U64.E4, U64.E5, U64.E6, U64.F4, U64.F5, U64.F6, U64.H3, U64.H5, U64.H7, U64.J1, U64.J9, U65.1, U65.3, U65.5
GND13: C209.1, C210.1, C211.2, C212.2, C213.2, C214.2, C215.2, C216.2, C217.2, C218.2, C219.2, C220.2, D92.C, D97.C, J92.1, J93.GND, J93.GND2, J94.3, J94.5, J94.9, J95.1, J97.4, J98.1, J98.2, R146.1, R148.1, R152.1, R154.1, S27.1, S27.2, S28.3, S28.4, U66.2, U67.2, U68.3, U69.A2, U69.A4, U69.A6, U69.B1, U69.B2, U69.B3, U69.B4, U69.B5, U69.B6, U69.B7, U69.D1, U69.D4, U69.D5, U69.D6, U69.D9, U69.E4, U69.E5, U69.E6, U69.F4, U69.F5, U69.F6, U69.H3, U69.H5, U69.H7, U69.J1, U69.J9, U70.1, U70.3, U70.5
GND14: C225.1, C226.1, C227.2, C228.2, C229.2, C230.2, C231.2, C232.2, C233.2, C234.2, C235.2, C236.2, D99.C, D104.C, J99.1, J100.GND, J100.GND2, J101.3, J101.5, J101.9, J102.1, J104.4, J105.1, J105.2, R157.1, R159.1, R163.1, R165.1, S29.1, S29.2, S30.3, S30.4, U71.2, U72.2, U73.3, U74.A2, U74.A4, U74.A6, U74.B1, U74.B2, U74.B3, U74.B4, U74.B5, U74.B6, U74.B7, U74.D1, U74.D4, U74.D5, U74.D6, U74.D9, U74.E4, U74.E5, U74.E6, U74.F4, U74.F5, U74.F6, U74.H3, U74.H5, U74.H7, U74.J1, U74.J9, U75.1, U75.3, U75.5
LORA_RF: C16.1, U3.A3
LORA_RF1: C29.1, U9.A3
LORA_RF2: C45.1, U14.A3
LORA_RF3: C61.1, U19.A3
LORA_RF4: C77.1, U24.A3
LORA_RF5: C93.1, U29.A3
LORA_RF6: C109.1, U34.A3
LORA_RF7: C125.1, U39.A3
LORA_RF8: C141.1, U44.A3
LORA_RF9: C157.1, U49.A3
LORA_RF10: C173.1, U54.A3
LORA_RF11: C189.1, U59.A3
LORA_RF12: C205.1, U64.A3
LORA_RF13: C221.1, U69.A3
LORA_RF14: C237.1, U74.A3
unnamed: R2.2, U1.5
unnamed: C7.2, U3.F9, Y1.P$2
unnamed: D1.C, R1.2
unnamed: R1.1, U1.1
unnamed: D5.A, R7.1
unnamed: LED.1, R4.2
unnamed: D7.A, R12.1
unnamed: C6.2, U3.E9, Y1.P$1
unnamed: D6.A, R8.1
unnamed: D4.A, R4.1
unnamed: C17.2, U6.6
unnamed: J8.FEED, U6.2
unnamed: C16.2, U6.4
unnamed: ISO.2, U2.5
unnamed: C1.1, C13.1, RTS.2
unnamed: D13.A, R13.1
unnamed: R20.2, U5.5
unnamed: D9.C, R21.2
unnamed: R21.1, U5.1
unnamed: C14.2, U9.F9, Y2.P$2
unnamed: C18.2, U9.E9, Y2.P$1
unnamed: D8.A, R19.1
unnamed: D14.A, R18.1
unnamed: D12.A, R15.1
unnamed: J14.FEED, U10.2
unnamed: C30.2, U10.6
unnamed: C29.2, U10.4
unnamed: ISO1.2, U7.5
unnamed: LED1.1, R13.2
unnamed: C31.1, C32.1, RTS1.2
unnamed: D20.A, R24.1
unnamed: R31.2, U11.5
unnamed: D16.C, R32.2
unnamed: R32.1, U11.1
unnamed: C33.2, U14.F9, Y3.P$2
unnamed: C34.2, U14.E9, Y3.P$1
unnamed: D15.A, R30.1
unnamed: D21.A, R29.1
unnamed: D19.A, R26.1
unnamed: J21.FEED, U15.2
unnamed: C46.2, U15.6
unnamed: C45.2, U15.4
unnamed: ISO2.2, U12.5
unnamed: LED2.1, R24.2
unnamed: C47.1, C48.1, RTS2.2
unnamed: D27.A, R35.1
unnamed: R42.2, U16.5
unnamed: D23.C, R43.2
unnamed: R43.1, U16.1
unnamed: C49.2, U19.F9, Y4.P$2
unnamed: C50.2, U19.E9, Y4.P$1
unnamed: D22.A, R41.1
unnamed: D28.A, R40.1
unnamed: D26.A, R37.1
unnamed: J28.FEED, U20.2
unnamed: C62.2, U20.6
unnamed: C61.2, U20.4
unnamed: ISO3.2, U17.5
unnamed: LED3.1, R35.2
unnamed: C63.1, C64.1, RTS3.2
unnamed: D34.A, R46.1
unnamed: R53.2, U21.5
unnamed: D30.C, R54.2
unnamed: R54.1, U21.1
unnamed: C65.2, U24.F9, Y5.P$2
unnamed: C66.2, U24.E9, Y5.P$1
unnamed: D29.A, R52.1
unnamed: D35.A, R51.1
unnamed: D33.A, R48.1
unnamed: J35.FEED, U25.2
unnamed: C78.2, U25.6
unnamed: C77.2, U25.4
unnamed: ISO4.2, U22.5
unnamed: LED4.1, R46.2
unnamed: C79.1, C80.1, RTS4.2
unnamed: D41.A, R57.1
unnamed: R64.2, U26.5
unnamed: D37.C, R65.2
unnamed: R65.1, U26.1
unnamed: C81.2, U29.F9, Y6.P$2
unnamed: C82.2, U29.E9, Y6.P$1
unnamed: D36.A, R63.1
unnamed: D42.A, R62.1
unnamed: D40.A, R59.1
unnamed: J42.FEED, U30.2
unnamed: C94.2, U30.6
unnamed: C93.2, U30.4
unnamed: ISO5.2, U27.5
unnamed: LED5.1, R57.2
unnamed: C95.1, C96.1, RTS5.2
unnamed: D48.A, R68.1
unnamed: R75.2, U31.5
unnamed: D44.C, R76.2
unnamed: R76.1, U31.1
unnamed: C97.2, U34.F9, Y7.P$2
unnamed: C98.2, U34.E9, Y7.P$1
unnamed: D43.A, R74.1
unnamed: D49.A, R73.1
unnamed: D47.A, R70.1
unnamed: J49.FEED, U35.2
unnamed: C110.2, U35.6
unnamed: C109.2, U35.4
unnamed: ISO6.2, U32.5
unnamed: LED6.1, R68.2
unnamed: C111.1, C112.1, RTS6.2
unnamed: D55.A, R79.1
unnamed: R86.2, U36.5
unnamed: D51.C, R87.2
unnamed: R87.1, U36.1
unnamed: C113.2, U39.F9, Y8.P$2
unnamed: C114.2, U39.E9, Y8.P$1
unnamed: D50.A, R85.1
unnamed: D56.A, R84.1
unnamed: D54.A, R81.1
unnamed: J56.FEED, U40.2
unnamed: C126.2, U40.6
unnamed: C125.2, U40.4
unnamed: ISO7.2, U37.5
unnamed: LED7.1, R79.2
unnamed: C127.1, C128.1, RTS7.2
unnamed: D62.A, R90.1
unnamed: R97.2, U41.5
unnamed: D58.C, R98.2
unnamed: R98.1, U41.1
unnamed: C129.2, U44.F9, Y9.P$2
unnamed: C130.2, U44.E9, Y9.P$1
unnamed: D57.A, R96.1
unnamed: D63.A, R95.1
unnamed: D61.A, R92.1
unnamed: J63.FEED, U45.2
unnamed: C142.2, U45.6
unnamed: C141.2, U45.4
unnamed: ISO8.2, U42.5
unnamed: LED8.1, R90.2
unnamed: C143.1, C144.1, RTS8.2
unnamed: D69.A, R101.1
unnamed: R108.2, U46.5
unnamed: D65.C, R109.2
unnamed: R109.1, U46.1
unnamed: C145.2, U49.F9, Y10.P$2
unnamed: C146.2, U49.E9, Y10.P$1
unnamed: D64.A, R107.1
unnamed: D70.A, R106.1
unnamed: D68.A, R103.1
unnamed: J70.FEED, U50.2
unnamed: C158.2, U50.6
unnamed: C157.2, U50.4
unnamed: ISO9.2, U47.5
unnamed: LED9.1, R101.2
unnamed: C159.1, C160.1, RTS9.2
unnamed: D76.A, R112.1
unnamed: R119.2, U51.5
unnamed: D72.C, R120.2
unnamed: R120.1, U51.1
unnamed: C161.2, U54.F9, Y11.P$2
unnamed: C162.2, U54.E9, Y11.P$1
unnamed: D71.A, R118.1
unnamed: D77.A, R117.1
unnamed: D75.A, R114.1
unnamed: J77.FEED, U55.2
unnamed: C174.2, U55.6
unnamed: C173.2, U55.4
unnamed: ISO10.2, U52.5
unnamed: LED10.1, R112.2
unnamed: C175.1, C176.1, RTS10.2
unnamed: D83.A, R123.1
unnamed: R130.2, U56.5
unnamed: D79.C, R131.2
unnamed: R131.1, U56.1
unnamed: C177.2, U59.F9, Y12.P$2
unnamed: C178.2, U59.E9, Y12.P$1
unnamed: D78.A, R129.1
unnamed: D84.A, R128.1
unnamed: D82.A, R125.1
unnamed: J84.FEED, U60.2
unnamed: C190.2, U60.6
unnamed: C189.2, U60.4
unnamed: ISO11.2, U57.5
unnamed: LED11.1, R123.2
unnamed: C191.1, C192.1, RTS11.2
unnamed: D90.A, R134.1
unnamed: R141.2, U61.5
unnamed: D86.C, R142.2
unnamed: R142.1, U61.1
unnamed: C193.2, U64.F9, Y13.P$2
unnamed: C194.2, U64.E9, Y13.P$1
unnamed: D85.A, R140.1
unnamed: D91.A, R139.1
unnamed: D89.A, R136.1
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
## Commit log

2020-10-05 Schematic Updated
2020-10-08 Added 4-layer board
2020-10-08 Cleaned up
2020-10-13 Fixed NM180100 footprint
2020-10-14 Renamed & rm LoRa reg
2020-10-15 Create prelim board fabrication files
2020-10-15 Update gerbers
2020-10-15 added gerbers
2020-10-21 Made suggested changes
2020-10-21 TP and Jumper addition
2020-10-22 Updated labels to buzzard vectors and more minor tweaks
    -also nudged some components near TX LED to make room for silk to avoid nearby mask.
    -added version text object to both sch sheets
    -redrew some sch to avoid 4-way nodes
    -added buzzard label to bottom LED disable jumper
    -moved ISO jumper to trace closed, added top silk label
    -added special ordering instructions with 4-layer board text on tDocu
2020-10-23 repo reorganization and started on readme
2020-10-23 Library work, added PROD_IDs to module and diplexer
2020-10-23 added 1/2/3/4 text obejcts in copper layers
    -also manually connected a GND pin on the CH340, due to islation increase it only had one side of the pad flowed. Might as well connect both sides.
    -nudge product name silk on bottom silk to avoid getting cutoff by usb millwork.
2020-10-23 Polarity silk markings added/moved outside package
2020-10-26 Made changes per review meeting, added FCC ID
2020-10-26 Design review changes
    -Updated EN on bottom silk to be input <EN]
    -Updated RESET on bottom silk to be input [!RESET!>
    -Repositioned LED jumper buzzard label
    -changed ISO jumper buzzard label to match inverted text style
    -Updated RX and TX bottom labels to input/output flag type
    -changed FCC info labels to buzzard
2020-10-27 RX/TX labels back to rounded, some minor tweaks to layer 15 for better gnd flow
    -fixed one right angle on layer 15, net D9/A7
    -nudged some traces and vias to allow for better ground flow on all pours
2020-10-28 Added NO jumper for RTS - RESET
2020-10-28 RTS jumper buzzard label
    -renamed jumper to "RTS"
    -added buzzard label
    -also moved user silk "10" to new button position
2020-10-28 checklist run
    -added text blurb explaining optional RTS jumper
    -approved one gnd wire stub off of ch340
2020-10-29 proto gerbers
2020-11-16 Fixed short from 3.3V to GND caused by USB connector mill holes
    Adjusted inner layer polygons to not pour under the USB connector. Previously these were shorting all planes together, causing a short between 3.3V NET and GND NET.
2020-11-18 Updating to USB-C-16P-4-LAYER-ISOLATED
    -This new footprint includes the isolation (aka cutout polygons). It is better to include these at the library lavel (rather than in the board, as it was previously).
    -Note, had to re-route VBUS, because the update also included moving the pads south to match the datasheet. This update commit history to the connector library here: https://github.com/sparkfun/Spark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
2020-12-04 PROD_ID on module update and schematic cleanup
    -The module PROD_ID SKU needed to be updated.
    -all vector fonts in schematic, and then rotation of 32K crysttal and reposition of name/value attributes.
2020-12-04 v10 production gerbers
2020-12-21 changed RTS jumper to normally closed trace
    -bumped version to v11 in brd and sch
    -adjusted RTS jumper paragraph in sch
2020-12-22 UART pin change
    -changed UART pin selection to match "standard" sparkfun SVL bootloader
    -TXO:GPIO48, RXI:GPIO49
    -Note, also moved "D10" net/button to GPIO4. This will also need to be configured with a custom "info zero" file to configure ASB to work.
2020-12-22 Added Boot net/pin (for ASB)
    -chose a boot pin (GPIO22). Note, we could not use the standard SFE pin of GPIO47, but this can be set during production programming of custom "info.0" binary.
    -connected RTS (post closed jumper) to boot net, including C13 and pull down R10.
    -left D10 on GPIO4 and is separate from boot circuit. It is soley a user button, similar to the Artemis Thing Plus design (although on a different GPIO#).
2020-12-22 Group review changes
    -removed wire stub on 3.3v via
    -adjusted routing off of tx LED
    -Moved 3.3V that was under the "VUSB" silk, to avoid overlap.
2020-12-22 Actual group review changes
2020-12-23 Eng Run of Checklist v11
    -vector fonts in sch corrected
    -updated version number in sheet 2 of sch
    -fixed text overlap on qwiic ra connector value text object
    -changed 1 0.1uF cap to same version (aka PROD_ID) as others to consolodate BOM
2020-12-23 v11 production panel BRD and gerbers
2021-01-29 adding info0 binary file and some documentation on creation/programming
2021-01-29 removing batch file option
    this is a bit more of a pain than it's worth here, because users may not have "jlink" setup in their PATHs and it also requires sending the device as an argument, where as the device is included in t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
2021-01-29 making programming instructions more concise
2021-02-05 product picture and links
    Add product picture
    Fix description
    Add links
2021-02-05 shorten product name
2021-02-08 Migrating eagle parts into SparkFun-Eagle-Libraries repo
    The module and diplexer are now in SparkFun-Microcontroller.lbr and SparkFun-RF.lbr for use in future designs. Deleting from this product repo to avoid having in two places.
